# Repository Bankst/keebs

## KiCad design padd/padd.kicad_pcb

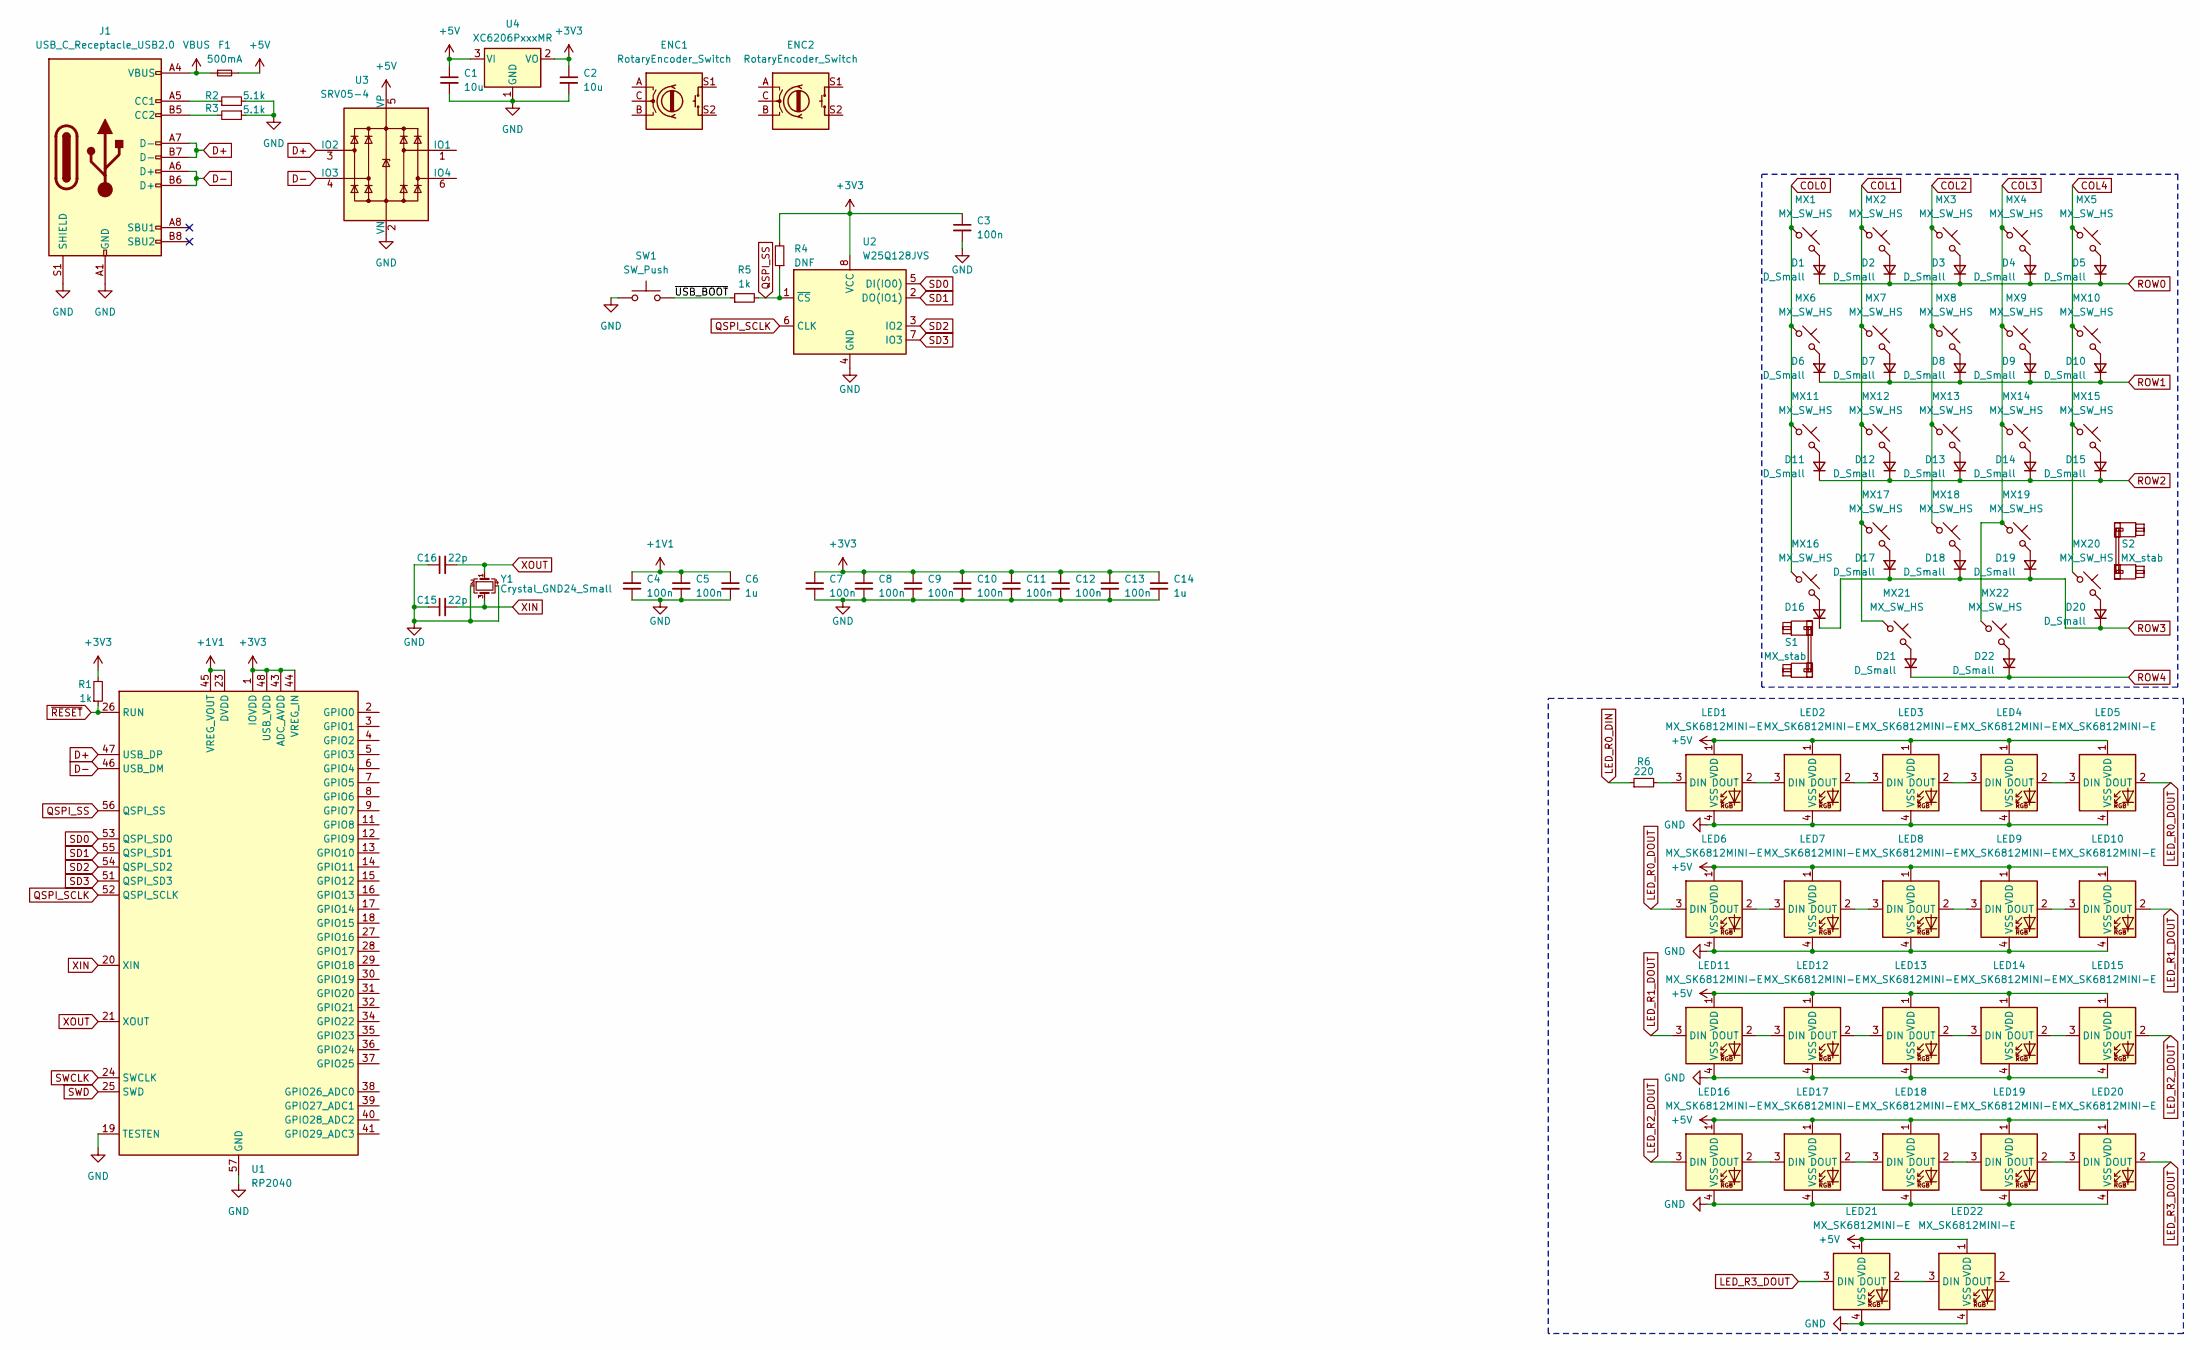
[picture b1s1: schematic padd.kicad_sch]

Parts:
C1, C2: 10u; C_0402_1005Metric
C3, C4, C5, C7, C8, C9, C10, C11, C12, C13: 100n; C_0402_1005Metric
C6, C14: 1u; C_0402_1005Metric
C15, C16: 22p; C_0402_1005Metric
D1, D2, D3, D4, D5, D6, D7, D8, D9, D10, D11, D12, D13, D14, D15, D16, D17, D18, D19, D20, D21, D22: D_Small; D_0402_1005Metric
ENC1, ENC2: RotaryEncoder_Switch; RotaryEncoder_Alps_EC11E-Switch_Vertical_H20mm
F1: 500mA; Fuse_1206_3216Metric
J1: USB_C_Receptacle_USB2.0; USB_C_Receptacle_HRO_TYPE-C-31-M-12
LED1, LED2, LED3, LED4, LED5, LED6, LED7, LED8, LED9, LED10, LED11, LED12, LED13, LED14, LED15, LED16, LED17, LED18, LED19, LED20, LED21, LED22: MX_SK6812MINI-E; LED_MX_6028R-ROT
MX1, MX2, MX3, MX4, MX5, MX6, MX7, MX8, MX9, MX10, MX11, MX12, MX13, MX14, MX15, MX16, MX17, MX18, MX19, MX20: MX_SW_HS; SW_MX_HS_1u
MX21, MX22: MX_SW_HS; SW_MX_HS_1.5u
R1, R5: 1k; R_0402_1005Metric
R2, R3: 5.1k; R_0402_1005Metric
R4: DNF; R_0402_1005Metric
R6: 220; R_0402_1005Metric
S1, S2: MX_stab; STAB_MX_P_2u
SW1: SW_Push; SW_Push_1P1T_NO_6x6mm_H9.5mm
U1: RP2040; QFN-56-1EP_7x7mm_P0.4mm_EP3.2x3.2mm
U2: W25Q128JVS; SOIC-8_5.23x5.23mm_P1.27mm
U3: SRV05-4; SOT-23-6-routable
U4: XC6206PxxxMR; SOT-23-6-routable
Y1: Crystal_GND24_Small; Crystal_SMD_2016-4Pin_2.0x1.6mm

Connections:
+1V1: C4.1, C5.1, C6.1, U1.23 (DVDD), U1.45 (VREG_VOUT), U1.50 (DVDD)
+3V3: C2.1, C3.1, C7.1, C8.1, C9.1, C10.1, C11.1, C12.1, C13.1, C14.1, R1.2, R4.2, U1.1 (IOVDD), U1.10 (IOVDD), U1.22 (IOVDD), U1.33 (IOVDD), U1.42 (IOVDD), U1.43 (ADC_AVDD), U1.44 (VREG_IN), U1.48 (USB_VDD), U1.49 (IOVDD), U2.8 (VCC), U4.2 (VO)
+5V: C1.1, F1.2, LED1.1 (VDD), LED2.1 (VDD), LED3.1 (VDD), LED4.1 (VDD), LED5.1 (VDD), LED6.1 (VDD), LED7.1 (VDD), LED8.1 (VDD), LED9.1 (VDD), LED10.1 (VDD), LED11.1 (VDD), LED12.1 (VDD), LED13.1 (VDD), LED14.1 (VDD), LED15.1 (VDD), LED16.1 (VDD), LED17.1 (VDD), LED18.1 (VDD), LED19.1 (VDD), LED20.1 (VDD), LED21.1 (VDD), LED22.1 (VDD), U3.5 (VP), U4.3 (VI)
/~USB_BOOT: R5.1, SW1.1
COL0: MX1.1, MX6.1, MX11.1, MX16.1
COL1: MX2.1, MX7.1, MX12.1, MX17.1, MX21.1
COL2: MX3.1, MX8.1, MX13.1, MX18.1
COL3: MX4.1, MX9.1, MX14.1, MX19.1, MX22.1
COL4: MX5.1, MX10.1, MX15.1, MX20.1
D+: J1.A7 (D-), J1.B7 (D-), U1.47 (USB_DP), U3.3 (IO2)
D-: J1.A6 (D+), J1.B6 (D+), U1.46 (USB_DM), U3.4 (IO3)
GND: C1.2, C2.2, C3.2, C4.2, C5.2, C6.2, C7.2, C8.2, C9.2, C10.2, C11.2, C12.2, C13.2, C14.2, C15.1, C16.1, J1.A1 (GND), J1.A12 (GND), J1.B1 (GND), J1.B12 (GND), J1.S1 (SHIELD), LED1.4 (VSS), LED2.4 (VSS), LED3.4 (VSS), LED4.4 (VSS), LED5.4 (VSS), LED6.4 (VSS), LED7.4 (VSS), LED8.4 (VSS), LED9.4 (VSS), LED10.4 (VSS), LED11.4 (VSS), LED12.4 (VSS), LED13.4 (VSS), LED14.4 (VSS), LED15.4 (VSS), LED16.4 (VSS), LED17.4 (VSS), LED18.4 (VSS), LED19.4 (VSS), LED20.4 (VSS), LED21.4 (VSS), LED22.4 (VSS), R2.2, R3.1, SW1.2, U1.19 (TESTEN), U1.57 (GND), U2.4 (GND), U3.2 (VN), U4.1 (GND), Y1.2, Y1.4
LED_R0_DIN: R6.1
LED_R0_DOUT: LED5.2 (DOUT), LED6.3 (DIN)
LED_R1_DOUT: LED10.2 (DOUT), LED11.3 (DIN)
LED_R2_DOUT: LED15.2 (DOUT), LED16.3 (DIN)
LED_R3_DOUT: LED20.2 (DOUT), LED21.3 (DIN)
unnamed: D1.2 (A), MX1.2
unnamed: D2.2 (A), MX2.2
unnamed: D3.2 (A), MX3.2
unnamed: D4.2 (A), MX4.2
unnamed: D5.2 (A), MX5.2
unnamed: D6.2 (A), MX6.2
unnamed: D7.2 (A), MX7.2
unnamed: D8.2 (A), MX8.2
unnamed: D9.2 (A), MX9.2
unnamed: D10.2 (A), MX10.2
unnamed: D11.2 (A), MX11.2
unnamed: D12.2 (A), MX12.2
unnamed: D13.2 (A), MX13.2
unnamed: D14.2 (A), MX14.2
unnamed: D15.2 (A), MX15.2
unnamed: D16.2 (A), MX16.2
unnamed: D17.2 (A), MX17.2
unnamed: D18.2 (A), MX18.2
unnamed: D19.2 (A), MX19.2
unnamed: D20.2 (A), MX20.2
unnamed: D21.2 (A), MX21.2
unnamed: D22.2 (A), MX22.2
unnamed: J1.A5 (CC1), R2.1
unnamed: J1.B5 (CC2), R3.2
unnamed: LED1.3 (DIN), R6.2
unnamed: LED1.2 (DOUT), LED2.3 (DIN)
unnamed: LED2.2 (DOUT), LED3.3 (DIN)
unnamed: LED3.2 (DOUT), LED4.3 (DIN)
unnamed: LED4.2 (DOUT), LED5.3 (DIN)
unnamed: LED6.2 (DOUT), LED7.3 (DIN)
unnamed: LED7.2 (DOUT), LED8.3 (DIN)
unnamed: LED8.2 (DOUT), LED9.3 (DIN)
unnamed: LED9.2 (DOUT), LED10.3 (DIN)
unnamed: LED11.2 (DOUT), LED12.3 (DIN)
unnamed: LED12.2 (DOUT), LED13.3 (DIN)
unnamed: LED13.2 (DOUT), LED14.3 (DIN)
unnamed: LED14.2 (DOUT), LED15.3 (DIN)
unnamed: LED16.2 (DOUT), LED17.3 (DIN)
unnamed: LED17.2 (DOUT), LED18.3 (DIN)
unnamed: LED18.2 (DOUT), LED19.3 (DIN)
unnamed: LED19.2 (DOUT), LED20.3 (DIN)
unnamed: LED21.2 (DOUT), LED22.3 (DIN)
QSPI_SCLK: U1.52 (QSPI_SCLK), U2.6 (CLK)
QSPI_SS: R4.1, R5.2, U1.56 (QSPI_SS), U2.1 (~CS)
ROW0: D1.1 (K), D2.1 (K), D3.1 (K), D4.1 (K), D5.1 (K)
ROW1: D6.1 (K), D7.1 (K), D8.1 (K), D9.1 (K), D10.1 (K)
ROW2: D11.1 (K), D12.1 (K), D13.1 (K), D14.1 (K), D15.1 (K)
ROW3: D16.1 (K), D17.1 (K), D18.1 (K), D19.1 (K), D20.1 (K)
ROW4: D21.1 (K), D22.1 (K)
SD0: U1.53 (QSPI_SD0), U2.5 (DI(IO0))
SD1: U1.55 (QSPI_SD1), U2.2 (DO(IO1))
SD2: U1.54 (QSPI_SD2), U2.3 (IO2)
SD3: U1.51 (QSPI_SD3), U2.7 (IO3)
SWCLK: U1.24 (SWCLK)
SWD: U1.25 (SWD)
VBUS: F1.1, J1.A4 (VBUS), J1.A9 (VBUS), J1.B4 (VBUS), J1.B9 (VBUS)
XIN: C15.2, U1.20 (XIN), Y1.3
XOUT: C16.2, U1.21 (XOUT), Y1.1
~RESET: R1.1, U1.26 (RUN)

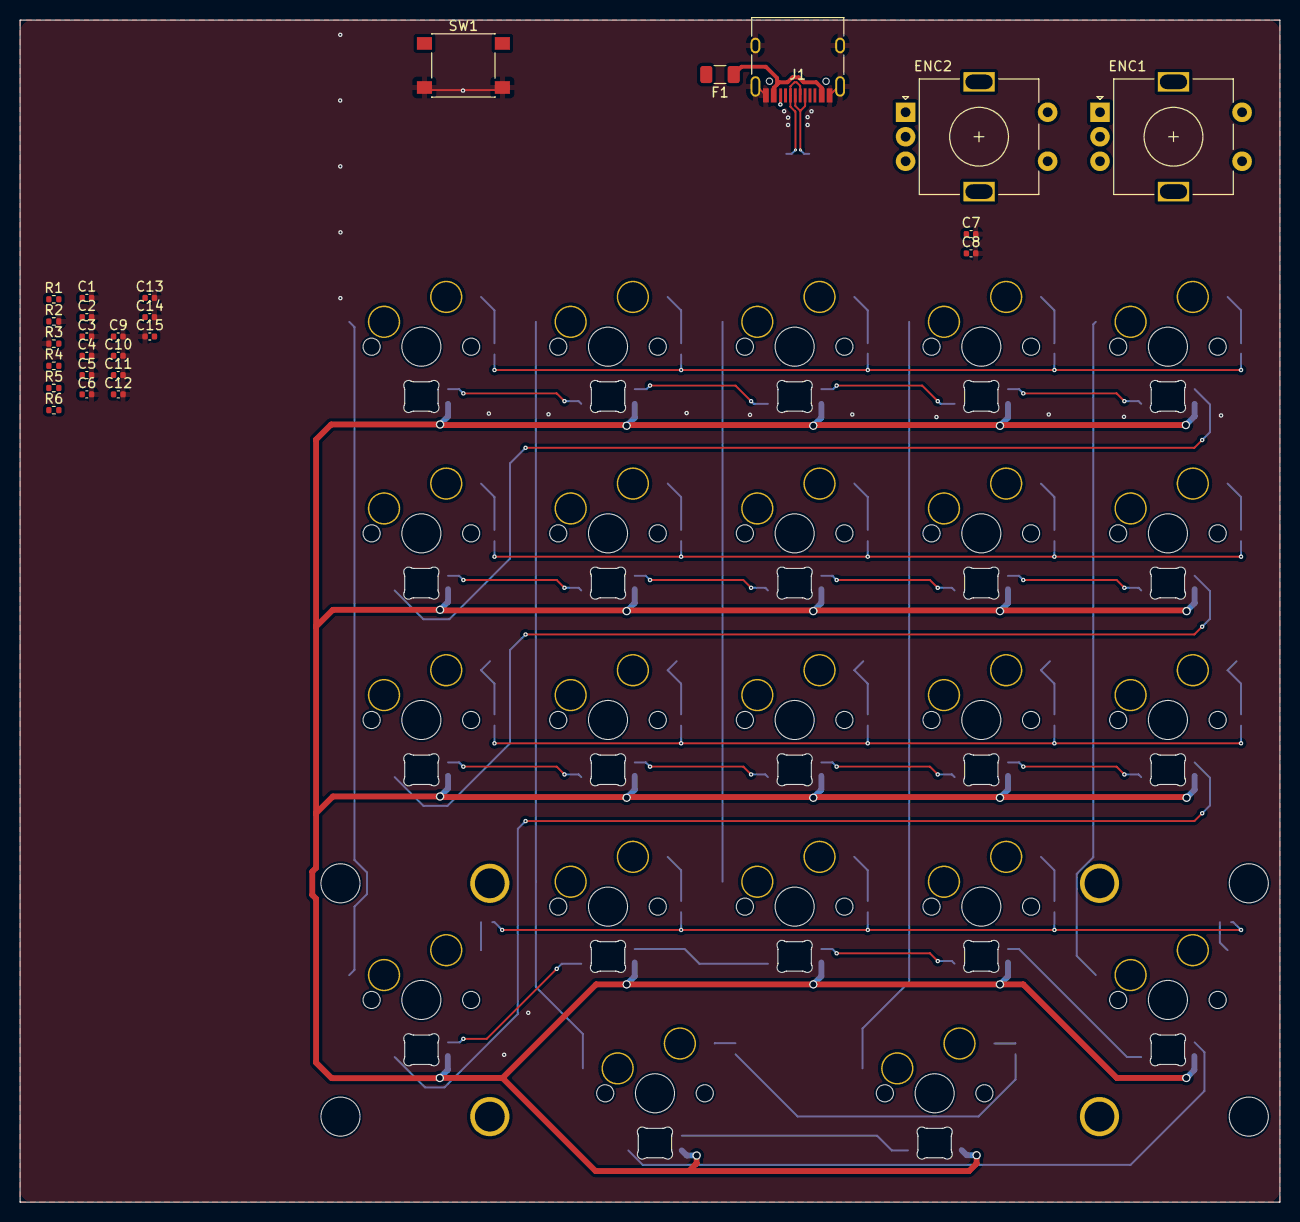
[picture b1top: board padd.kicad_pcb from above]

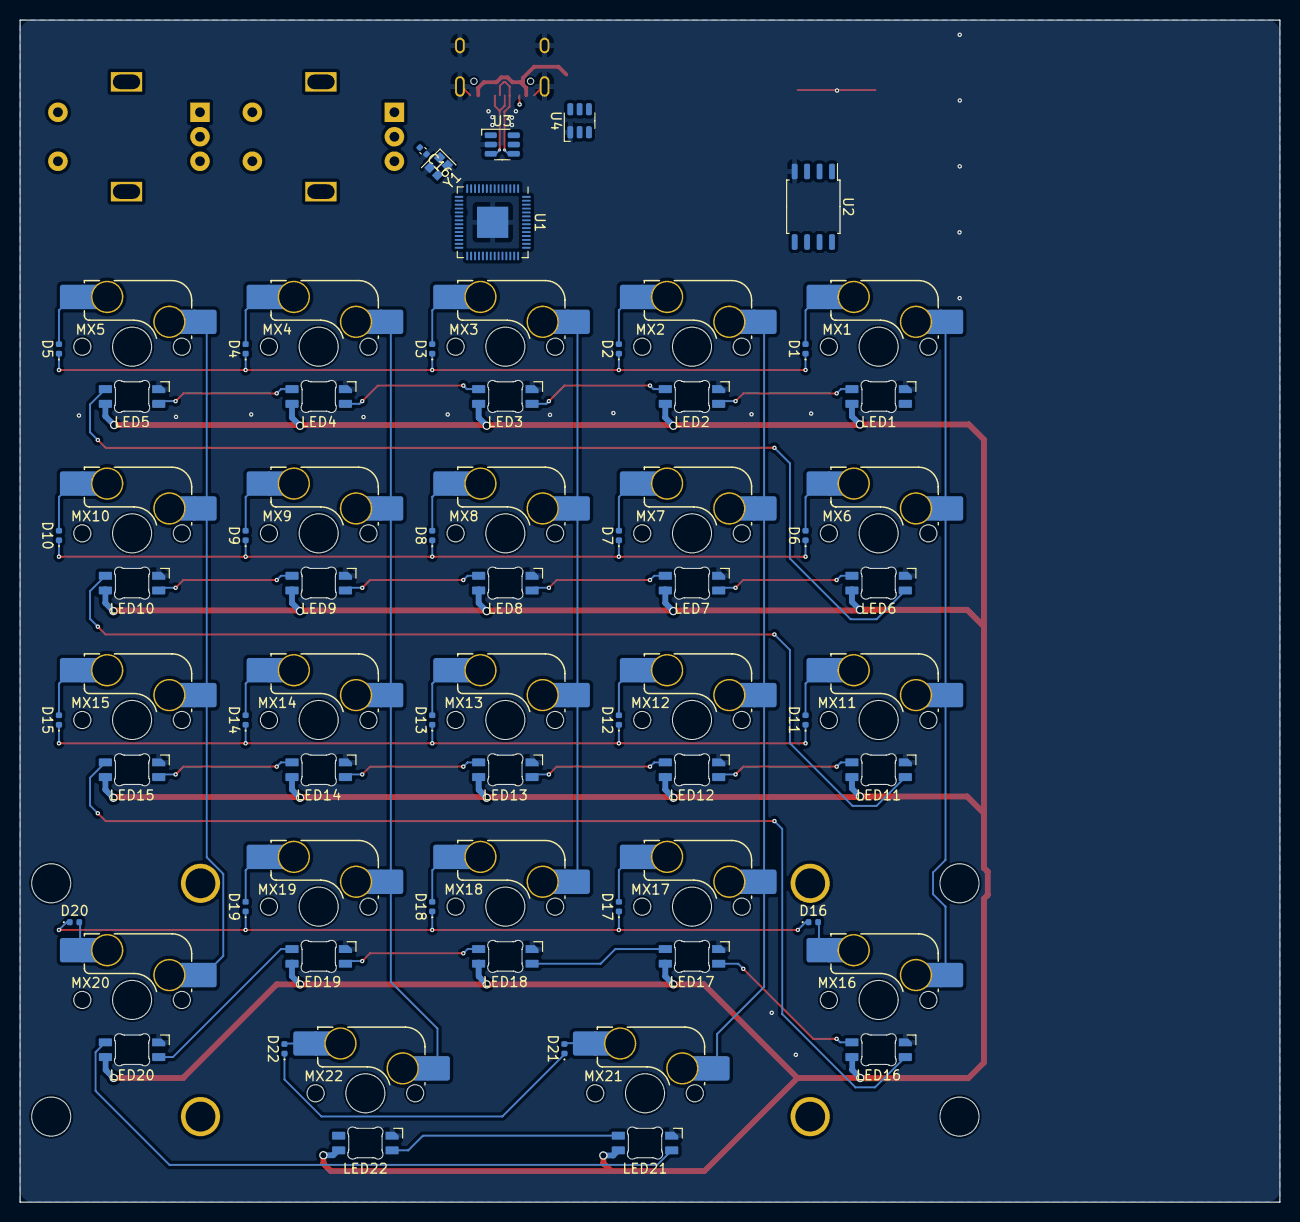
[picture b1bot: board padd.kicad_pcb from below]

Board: 2 copper layers, 128.6 x 120.6 mm, 100 parts (72 on the bottom side), 73 nets.

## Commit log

2024-01-02 move to rp2040 onboard
